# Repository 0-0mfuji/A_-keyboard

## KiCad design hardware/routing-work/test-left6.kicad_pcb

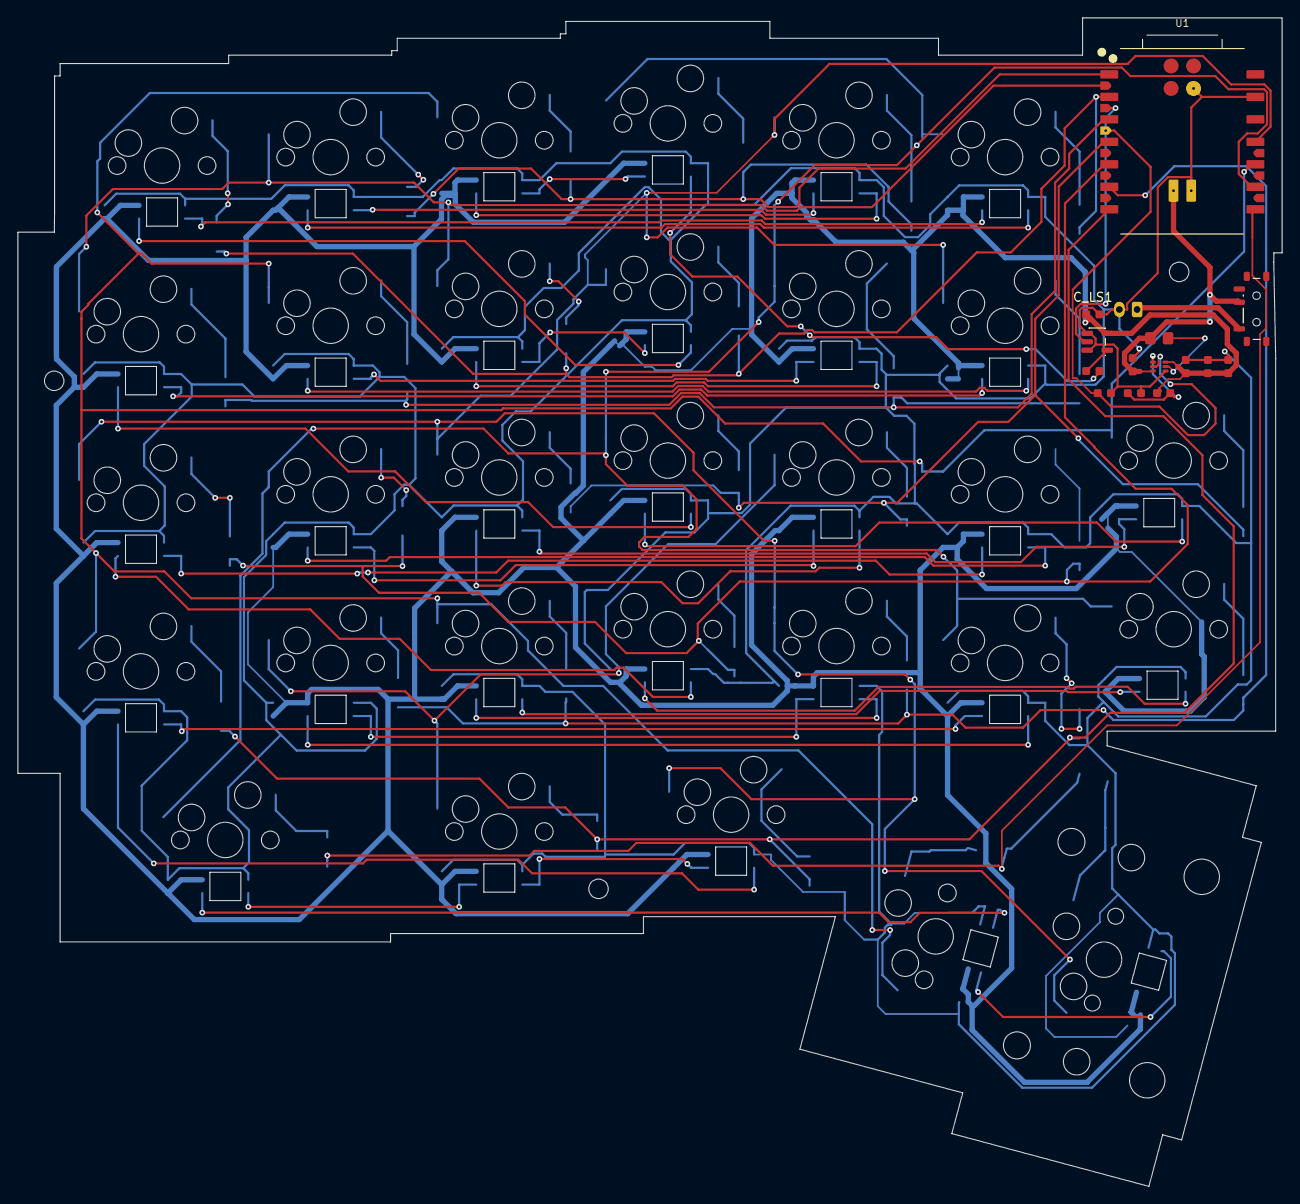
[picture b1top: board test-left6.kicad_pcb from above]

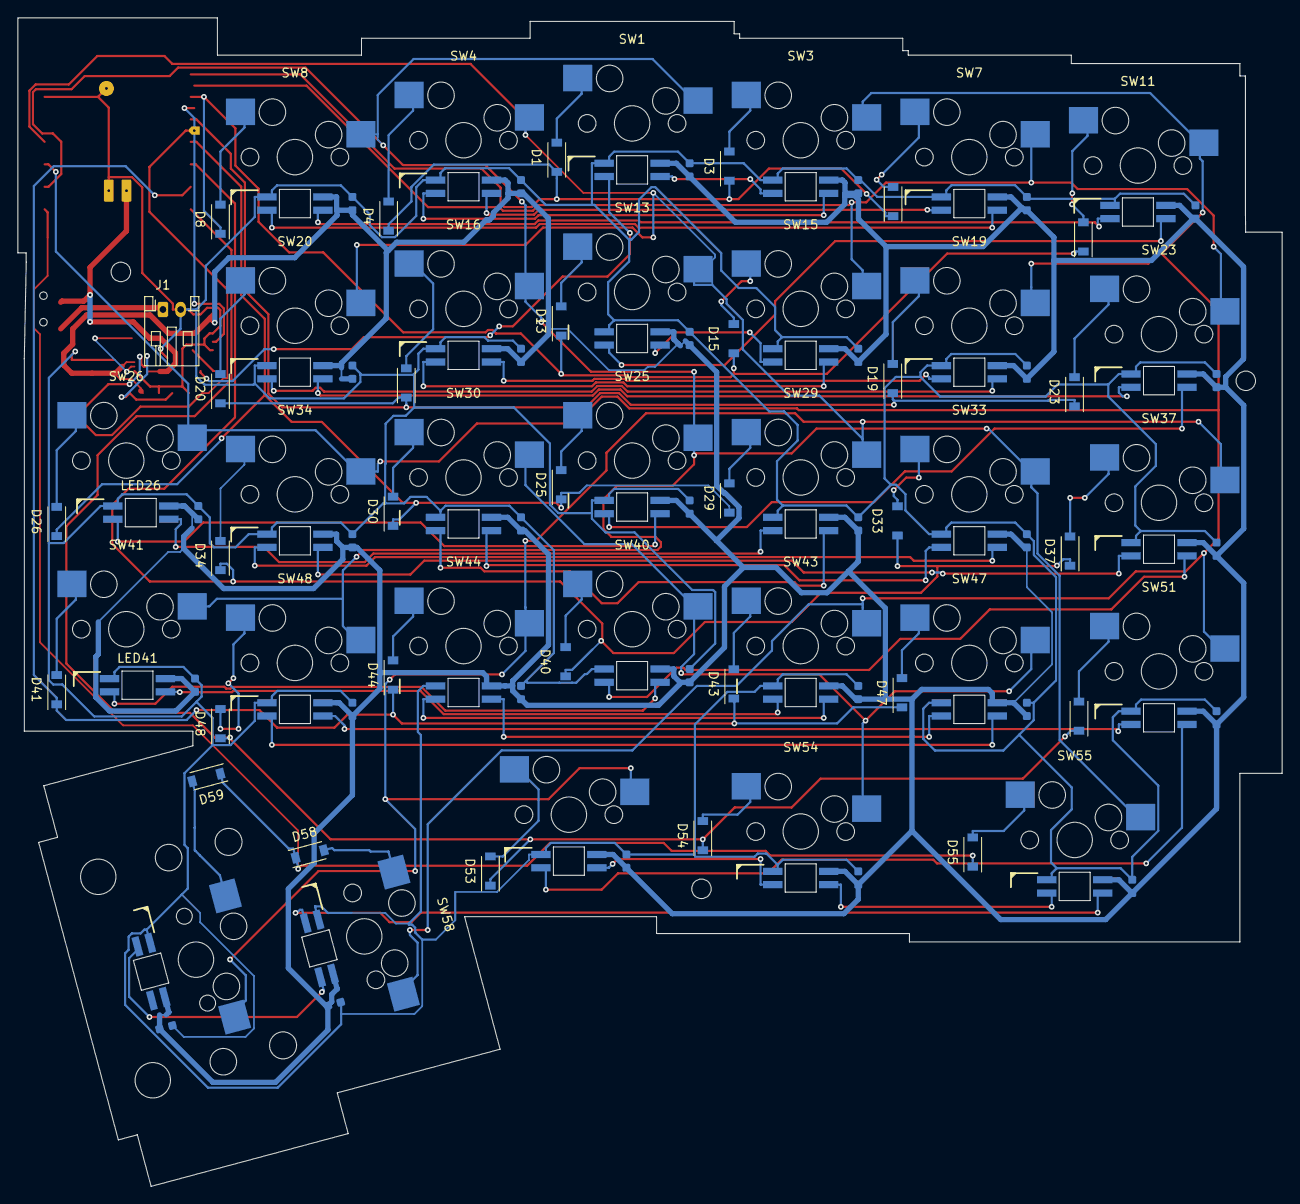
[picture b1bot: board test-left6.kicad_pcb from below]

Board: 2 copper layers, 142.8 x 132.0 mm, 144 parts (94 on the bottom side), 83 nets.

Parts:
C_LS1: 100nF; C_0603
C_RGB1, C_RGB3, C_RGB4, C_RGB7, C_RGB8, C_RGB11, C_RGB13, C_RGB15, C_RGB16, C_RGB19, C_RGB20, C_RGB23, C_RGB25, C_RGB26, C_RGB29, C_RGB30, C_RGB33, C_RGB34, C_RGB37, C_RGB40, C_RGB41, C_RGB43, C_RGB44, C_RGB47, C_RGB48, C_RGB51, C_RGB53, C_RGB54, C_RGB55, C_RGB58, C_RGB59: 100nF; C_0603
C_RGB_BULK1: 100uF; C_0603
C_RGB_IN1: 10uF; C_0603
C_RGB_OUT1_1, C_RGB_OUT2_1: 22uF; C_0603
D1, D3, D4, D7, D8, D11, D13, D15, D16, D19, D20, D23, D25, D26, D29, D30, D33, D34, D37, D40, D41, D43, D44, D47, D48, D51, D53, D54, D55, D58, D59: 1N4148W; SOD123
H1, H2, H3: M2 NPTH clearance; MountingHole
J1: JST PH 2.0 2-pin; BatteryConnector_JST_PH2
LED1, LED3, LED4, LED7, LED8, LED11, LED13, LED15, LED16, LED19, LED20, LED23, LED25, LED26, LED29, LED30, LED33, LED34, LED37, LED40, LED41, LED43, LED44, LED47, LED48, LED51, LED53, LED54, LED55, LED58, LED59: SK6812MINI-E; LED_SK6812MINI-E_BL
L_RGB1: 1uH; L_1008
R_RGB_DATA1: 220R; R_0603
R_RGB_EN_PD1: 100k; R_0603
R_RGB_FB_BOT1: 100k; R_0603
R_RGB_FB_TOP1: 732k; R_0603
STAB1, STAB2: MX stabilizer NPTH; MXStabilizerHole
SW1, SW3, SW4, SW7, SW8, SW11, SW13, SW15, SW16, SW19, SW20, SW25, SW26, SW29, SW30, SW33, SW34, SW40, SW41, SW43, SW44, SW47, SW48: MX; MX_Hotswap_1u
SW23, SW37, SW51, SW53: MX; MX_Hotswap_1.25u
SW54, SW58: MX; MX_Hotswap_1.5u
SW55: MX; MX_Hotswap_1.75u
SW59: MX; MX_Hotswap_2.25u
SWP1: MSK-12C02 slide switch; PowerSwitch_MSK12C02
U1: XIAO nRF52840 Plus (SMD); XIAO_NRF52840_PLUS
U_LS1: SN74AHCT1G125
U_RGB1: TPS61023

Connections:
/COL0: SW1.1, SW8.1, SW16.1, SW25.1, SW33.1, SW41.1, SW48.1, SW55.1, U1.9
/COL1: SW3.1, SW11.1, SW19.1, SW26.1, SW34.1, SW43.1, SW51.1, SW58.1, U1.10
/COL2: SW4.1, SW13.1, SW20.1, SW29.1, SW37.1, SW44.1, SW53.1, SW59.1, U1.11
/COL3: SW7.1, SW15.1, SW23.1, SW30.1, SW40.1, SW47.1, SW54.1, U1.15
/GND_LEFT: C_LS1.2, C_RGB1.2, C_RGB3.2, C_RGB4.2, C_RGB7.2, C_RGB8.2, C_RGB11.2, C_RGB13.2, C_RGB15.2, C_RGB16.2, C_RGB19.2, C_RGB20.2, C_RGB23.2, C_RGB25.2, C_RGB26.2, C_RGB29.2, C_RGB30.2, C_RGB33.2, C_RGB34.2, C_RGB37.2, C_RGB40.2, C_RGB41.2, C_RGB43.2, C_RGB44.2, C_RGB47.2, C_RGB48.2, C_RGB51.2, C_RGB53.2, C_RGB54.2, C_RGB55.2, C_RGB58.2, C_RGB59.2, C_RGB_BULK1.2, C_RGB_IN1.2, C_RGB_OUT1_1.2, C_RGB_OUT2_1.2, J1.2, LED1.2, LED3.2, LED4.2, LED7.2, LED8.2, LED11.2, LED13.2, LED15.2, LED16.2, LED19.2, LED20.2, LED23.2, LED25.2, LED26.2, LED29.2, LED30.2, LED33.2, LED34.2, LED37.2, LED40.2, LED41.2, LED43.2, LED44.2, LED47.2, LED48.2, LED51.2, LED53.2, LED54.2, LED55.2, LED58.2, LED59.2, R_RGB_EN_PD1.2, R_RGB_FB_BOT1.2, U1.13, U1.27, U1.29, U_LS1.1, U_LS1.3, U_RGB1.4
/RGB_5V_LEFT: C_LS1.1, C_RGB1.1, C_RGB3.1, C_RGB4.1, C_RGB7.1, C_RGB8.1, C_RGB11.1, C_RGB13.1, C_RGB15.1, C_RGB16.1, C_RGB19.1, C_RGB20.1, C_RGB23.1, C_RGB25.1, C_RGB26.1, C_RGB29.1, C_RGB30.1, C_RGB33.1, C_RGB34.1, C_RGB37.1, C_RGB40.1, C_RGB41.1, C_RGB43.1, C_RGB44.1, C_RGB47.1, C_RGB48.1, C_RGB51.1, C_RGB53.1, C_RGB54.1, C_RGB55.1, C_RGB58.1, C_RGB59.1, C_RGB_BULK1.1, C_RGB_OUT1_1.1, C_RGB_OUT2_1.1, LED1.1, LED3.1, LED4.1, LED7.1, LED8.1, LED11.1, LED13.1, LED15.1, LED16.1, LED19.1, LED20.1, LED23.1, LED25.1, LED26.1, LED29.1, LED30.1, LED33.1, LED34.1, LED37.1, LED40.1, LED41.1, LED43.1, LED44.1, LED47.1, LED48.1, LED51.1, LED53.1, LED54.1, LED55.1, LED58.1, LED59.1, R_RGB_FB_TOP1.1, U_LS1.5, U_RGB1.6
/RGB_DATA_LEFT: U1.16, U_LS1.2
/RGB_DATA_SHIFTED_LEFT: LED1.3, R_RGB_DATA1.2
/RGB_EN_LEFT: R_RGB_EN_PD1.1, U1.17, U_RGB1.2
/ROW0: D1.1, D3.1, D4.1, D7.1, U1.1
/ROW1: D8.1, D11.1, D13.1, D15.1, U1.2
/ROW2: D16.1, D19.1, D20.1, D23.1, U1.3
/ROW3: D25.1, D26.1, D29.1, D30.1, U1.4
/ROW4: D33.1, D34.1, D37.1, D40.1, U1.5
/ROW5: D41.1, D43.1, D44.1, D47.1, U1.6
/ROW6: D48.1, D51.1, D53.1, D54.1, U1.7
/ROW7: D55.1, D58.1, D59.1, U1.8
/VBAT_LEFT: C_RGB_IN1.1, L_RGB1.1, SWP1.2, U1.28, U_RGB1.3
/matrix/SW1_A: D1.2, SW1.2
/matrix/SW3_A: D3.2, SW3.2
/matrix/SW4_A: D4.2, SW4.2
/matrix/SW7_A: D7.2, SW7.2
/matrix/SW8_A: D8.2, SW8.2
/matrix/SW11_A: D11.2, SW11.2
/matrix/SW13_A: D13.2, SW13.2
/matrix/SW15_A: D15.2, SW15.2
/matrix/SW16_A: D16.2, SW16.2
/matrix/SW19_A: D19.2, SW19.2
/matrix/SW20_A: D20.2, SW20.2
/matrix/SW23_A: D23.2, SW23.2
/matrix/SW25_A: D25.2, SW25.2
/matrix/SW26_A: D26.2, SW26.2
/matrix/SW29_A: D29.2, SW29.2
/matrix/SW30_A: D30.2, SW30.2
/matrix/SW33_A: D33.2, SW33.2
/matrix/SW34_A: D34.2, SW34.2
/matrix/SW37_A: D37.2, SW37.2
/matrix/SW40_A: D40.2, SW40.2
/matrix/SW41_A: D41.2, SW41.2
/matrix/SW43_A: D43.2, SW43.2
/matrix/SW44_A: D44.2, SW44.2
/matrix/SW47_A: D47.2, SW47.2
/matrix/SW48_A: D48.2, SW48.2
/matrix/SW51_A: D51.2, SW51.2
/matrix/SW53_A: D53.2, SW53.2
/matrix/SW54_A: D54.2, SW54.2
/matrix/SW55_A: D55.2, SW55.2
/matrix/SW58_A: D58.2, SW58.2
/matrix/SW59_A: D59.2, SW59.2
/power/BAT_RAW_LEFT: J1.1, SWP1.1
/power/RGB_FB_LEFT: R_RGB_FB_BOT1.1, R_RGB_FB_TOP1.2, U_RGB1.1
/power/RGB_SHIFTED_LEFT: R_RGB_DATA1.1, U_LS1.4
/power/RGB_SW_LEFT: L_RGB1.2, U_RGB1.5
/rgb/RGB_LED_left_0: LED1.4, LED3.3
/rgb/RGB_LED_left_1: LED3.4, LED4.3
/rgb/RGB_LED_left_2: LED4.4, LED7.3
/rgb/RGB_LED_left_3: LED7.4, LED8.3
/rgb/RGB_LED_left_4: LED8.4, LED11.3
/rgb/RGB_LED_left_5: LED11.4, LED13.3
/rgb/RGB_LED_left_6: LED13.4, LED15.3
/rgb/RGB_LED_left_7: LED15.4, LED16.3
/rgb/RGB_LED_left_8: LED16.4, LED19.3
/rgb/RGB_LED_left_9: LED19.4, LED20.3
/rgb/RGB_LED_left_10: LED20.4, LED23.3
/rgb/RGB_LED_left_11: LED23.4, LED25.3
/rgb/RGB_LED_left_12: LED25.4, LED26.3
/rgb/RGB_LED_left_13: LED26.4, LED29.3
/rgb/RGB_LED_left_14: LED29.4, LED30.3
/rgb/RGB_LED_left_15: LED30.4, LED33.3
/rgb/RGB_LED_left_16: LED33.4, LED34.3
/rgb/RGB_LED_left_17: LED34.4, LED37.3
/rgb/RGB_LED_left_18: LED37.4, LED40.3
/rgb/RGB_LED_left_19: LED40.4, LED41.3
/rgb/RGB_LED_left_20: LED41.4, LED43.3
/rgb/RGB_LED_left_21: LED43.4, LED44.3
/rgb/RGB_LED_left_22: LED44.4, LED47.3
/rgb/RGB_LED_left_23: LED47.4, LED48.3
/rgb/RGB_LED_left_24: LED48.4, LED51.3
/rgb/RGB_LED_left_25: LED51.4, LED53.3
/rgb/RGB_LED_left_26: LED53.4, LED54.3
/rgb/RGB_LED_left_27: LED54.4, LED55.3
/rgb/RGB_LED_left_28: LED55.4, LED58.3
/rgb/RGB_LED_left_29: LED58.4, LED59.3

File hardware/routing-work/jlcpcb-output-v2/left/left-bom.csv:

"Refs","Value","Footprint","Qty","DNP"
"C_LS1","100nF","Keyboard:C_0603","1",""
"C_RGB1","100nF","Keyboard:C_0603","1",""
"C_RGB3","100nF","Keyboard:C_0603","1",""
"C_RGB4","100nF","Keyboard:C_0603","1",""
"C_RGB7","100nF","Keyboard:C_0603","1",""
"C_RGB8","100nF","Keyboard:C_0603","1",""
"C_RGB11","100nF","Keyboard:C_0603","1",""
"C_RGB13","100nF","Keyboard:C_0603","1",""
"C_RGB15","100nF","Keyboard:C_0603","1",""
"C_RGB16","100nF","Keyboard:C_0603","1",""
"C_RGB19","100nF","Keyboard:C_0603","1",""
"C_RGB20","100nF","Keyboard:C_0603","1",""
"C_RGB23","100nF","Keyboard:C_0603","1",""
"C_RGB25","100nF","Keyboard:C_0603","1",""
"C_RGB26","100nF","Keyboard:C_0603","1",""
"C_RGB29","100nF","Keyboard:C_0603","1",""
"C_RGB30","100nF","Keyboard:C_0603","1",""
"C_RGB33","100nF","Keyboard:C_0603","1",""
"C_RGB34","100nF","Keyboard:C_0603","1",""
"C_RGB37","100nF","Keyboard:C_0603","1",""
"C_RGB40","100nF","Keyboard:C_0603","1",""
"C_RGB41","100nF","Keyboard:C_0603","1",""
"C_RGB43","100nF","Keyboard:C_0603","1",""
"C_RGB44","100nF","Keyboard:C_0603","1",""
"C_RGB47","100nF","Keyboard:C_0603","1",""
"C_RGB48","100nF","Keyboard:C_0603","1",""
"C_RGB51","100nF","Keyboard:C_0603","1",""
"C_RGB53","100nF","Keyboard:C_0603","1",""
"C_RGB54","100nF","Keyboard:C_0603","1",""
"C_RGB55","100nF","Keyboard:C_0603","1",""
"C_RGB58","100nF","Keyboard:C_0603","1",""
"C_RGB59","100nF","Keyboard:C_0603","1",""
"C_RGB_BULK1","100uF","Keyboard:C_0603","1",""
"C_RGB_IN1","10uF","Keyboard:C_0603","1",""
"C_RGB_OUT1_1","22uF","Keyboard:C_0603","1",""
"C_RGB_OUT2_1","22uF","Keyboard:C_0603","1",""
"D1","1N4148W","Keyboard:SOD123","1",""
"D3","1N4148W","Keyboard:SOD123","1",""
"D4","1N4148W","Keyboard:SOD123","1",""
"D7","1N4148W","Keyboard:SOD123","1",""
"D8","1N4148W","Keyboard:SOD123","1",""
"D11","1N4148W","Keyboard:SOD123","1",""
"D13","1N4148W","Keyboard:SOD123","1",""
"D15","1N4148W","Keyboard:SOD123","1",""
"D16","1N4148W","Keyboard:SOD123","1",""
"D19","1N4148W","Keyboard:SOD123","1",""
"D20","1N4148W","Keyboard:SOD123","1",""
"D23","1N4148W","Keyboard:SOD123","1",""
"D25","1N4148W","Keyboard:SOD123","1",""
"D26","1N4148W","Keyboard:SOD123","1",""
"D29","1N4148W","Keyboard:SOD123","1",""
"D30","1N4148W","Keyboard:SOD123","1",""
"D33","1N4148W","Keyboard:SOD123","1",""
"D34","1N4148W","Keyboard:SOD123","1",""
"D37","1N4148W","Keyboard:SOD123","1",""
"D40","1N4148W","Keyboard:SOD123","1",""
"D41","1N4148W","Keyboard:SOD123","1",""
"D43","1N4148W","Keyboard:SOD123","1",""
"D44","1N4148W","Keyboard:SOD123","1",""
"D47","1N4148W","Keyboard:SOD123","1",""
"D48","1N4148W","Keyboard:SOD123","1",""
"D51","1N4148W","Keyboard:SOD123","1",""
"D53","1N4148W","Keyboard:SOD123","1",""
"D54","1N4148W","Keyboard:SOD123","1",""
"D55","1N4148W","Keyboard:SOD123","1",""
"D58","1N4148W","Keyboard:SOD123","1",""
"D59","1N4148W","Keyboard:SOD123","1",""
"J1","JST PH 2.0 2-pin","Keyboard:BatteryConnector_JST_PH2","1",""
"LED1","SK6812MINI-E","Keyboard:LED_SK6812MINI-E_BL","1",""
"LED3","SK6812MINI-E","Keyboard:LED_SK6812MINI-E_BL","1",""
"LED4","SK6812MINI-E","Keyboard:LED_SK6812MINI-E_BL","1",""
"LED7","SK6812MINI-E","Keyboard:LED_SK6812MINI-E_BL","1",""
"LED8","SK6812MINI-E","Keyboard:LED_SK6812MINI-E_BL","1",""
"LED11","SK6812MINI-E","Keyboard:LED_SK6812MINI-E_BL","1",""
"LED13","SK6812MINI-E","Keyboard:LED_SK6812MINI-E_BL","1",""
"LED15","SK6812MINI-E","Keyboard:LED_SK6812MINI-E_BL","1",""
"LED16","SK6812MINI-E","Keyboard:LED_SK6812MINI-E_BL","1",""
"LED19","SK6812MINI-E","Keyboard:LED_SK6812MINI-E_BL","1",""
"LED20","SK6812MINI-E","Keyboard:LED_SK6812MINI-E_BL","1",""
"LED23","SK6812MINI-E","Keyboard:LED_SK6812MINI-E_BL","1",""
"LED25","SK6812MINI-E","Keyboard:LED_SK6812MINI-E_BL","1",""
"LED26","SK6812MINI-E","Keyboard:LED_SK6812MINI-E_BL","1",""
"LED29","SK6812MINI-E","Keyboard:LED_SK6812MINI-E_BL","1",""
"LED30","SK6812MINI-E","Keyboard:LED_SK6812MINI-E_BL","1",""
"LED33","SK6812MINI-E","Keyboard:LED_SK6812MINI-E_BL","1",""
"LED34","SK6812MINI-E","Keyboard:LED_SK6812MINI-E_BL","1",""
"LED37","SK6812MINI-E","Keyboard:LED_SK6812MINI-E_BL","1",""
"LED40","SK6812MINI-E","Keyboard:LED_SK6812MINI-E_BL","1",""
"LED41","SK6812MINI-E","Keyboard:LED_SK6812MINI-E_BL","1",""
"LED43","SK6812MINI-E","Keyboard:LED_SK6812MINI-E_BL","1",""
"LED44","SK6812MINI-E","Keyboard:LED_SK6812MINI-E_BL","1",""
"LED47","SK6812MINI-E","Keyboard:LED_SK6812MINI-E_BL","1",""
"LED48","SK6812MINI-E","Keyboard:LED_SK6812MINI-E_BL","1",""
"LED51","SK6812MINI-E","Keyboard:LED_SK6812MINI-E_BL","1",""
"LED53","SK6812MINI-E","Keyboard:LED_SK6812MINI-E_BL","1",""
"LED54","SK6812MINI-E","Keyboard:LED_SK6812MINI-E_BL","1",""
"LED55","SK6812MINI-E","Keyboard:LED_SK6812MINI-E_BL","1",""
"LED58","SK6812MINI-E","Keyboard:LED_SK6812MINI-E_BL","1",""
"LED59","SK6812MINI-E","Keyboard:LED_SK6812MINI-E_BL","1",""
"L_RGB1","1uH","Keyboard:L_1008","1",""
"R_RGB_DATA1","220R","Keyboard:R_0603","1",""
"R_RGB_EN_PD1","100k","Keyboard:R_0603","1",""
"R_RGB_FB_BOT1","100k","Keyboard:R_0603","1",""
"R_RGB_FB_TOP1","732k","Keyboard:R_0603","1",""
"SW1","MX","Keyboard:MX_Hotswap_1u","1",""
"SW3","MX","Keyboard:MX_Hotswap_1u","1",""
"SW4","MX","Keyboard:MX_Hotswap_1u","1",""
"SW7","MX","Keyboard:MX_Hotswap_1u","1",""
"SW8","MX","Keyboard:MX_Hotswap_1u","1",""
"SW11","MX","Keyboard:MX_Hotswap_1u","1",""
"SW13","MX","Keyboard:MX_Hotswap_1u","1",""
"SW15","MX","Keyboard:MX_Hotswap_1u","1",""
"SW16","MX","Keyboard:MX_Hotswap_1u","1",""
"SW19","MX","Keyboard:MX_Hotswap_1u","1",""
"SW20","MX","Keyboard:MX_Hotswap_1u","1",""
"SW23","MX","Keyboard:MX_Hotswap_1.25u","1",""
"SW25","MX","Keyboard:MX_Hotswap_1u","1",""
"SW26","MX","Keyboard:MX_Hotswap_1u","1",""
"SW29","MX","Keyboard:MX_Hotswap_1u","1",""
"SW30","MX","Keyboard:MX_Hotswap_1u","1",""
"SW33","MX","Keyboard:MX_Hotswap_1u","1",""
"SW34","MX","Keyboard:MX_Hotswap_1u","1",""
"SW37","MX","Keyboard:MX_Hotswap_1.25u","1",""
"SW40","MX","Keyboard:MX_Hotswap_1u","1",""
"SW41","MX","Keyboard:MX_Hotswap_1u","1",""
"SW43","MX","Keyboard:MX_Hotswap_1u","1",""
"SW44","MX","Keyboard:MX_Hotswap_1u","1",""
"SW47","MX","Keyboard:MX_Hotswap_1u","1",""
"SW48","MX","Keyboard:MX_Hotswap_1u","1",""
"SW51","MX","Keyboard:MX_Hotswap_1.25u","1",""
"SW53","MX","Keyboard:MX_Hotswap_1.25u","1",""
"SW54","MX","Keyboard:MX_Hotswap_1.5u","1",""
"SW55","MX","Keyboard:MX_Hotswap_1.75u","1",""
"SW58","MX","Keyboard:MX_Hotswap_1.5u","1",""
"SW59","MX","Keyboard:MX_Hotswap_2.25u","1",""
"SWP1","MSK-12C02 slide switch","Keyboard:PowerSwitch_MSK12C02","1",""
"U1","XIAO nRF52840 Plus (SMD)","Keyboard:XIAO_NRF52840_PLUS","1",""
"U_LS1","SN74AHCT1G125","Keyboard:SN74AHCT1G125","1",""
"U_RGB1","TPS61023","Keyboard:TPS61023","1",""
